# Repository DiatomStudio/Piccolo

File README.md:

# Piccolo, the tiny cnc bot #

A pocket sized open source CNC-bot.

Using laser-cutting, off-the-shelf hardware and Arduino, you can make your own simple 3 axis robot. Attach a brush or pen to make a quick drawing robot, or extend Piccolo with sensors, custom toolheads, or by using multiple Piccolos together. Experiment with 2D or 3D digital fabrication at a small scale!

For more info please see [www.piccolo.cc](http://www.piccolo.cc)

[Piccolo Flickr Pool](http://www.flickr.com/groups/1929303@N21/)

[www.diatom.cc](http://www.diatom.cc)

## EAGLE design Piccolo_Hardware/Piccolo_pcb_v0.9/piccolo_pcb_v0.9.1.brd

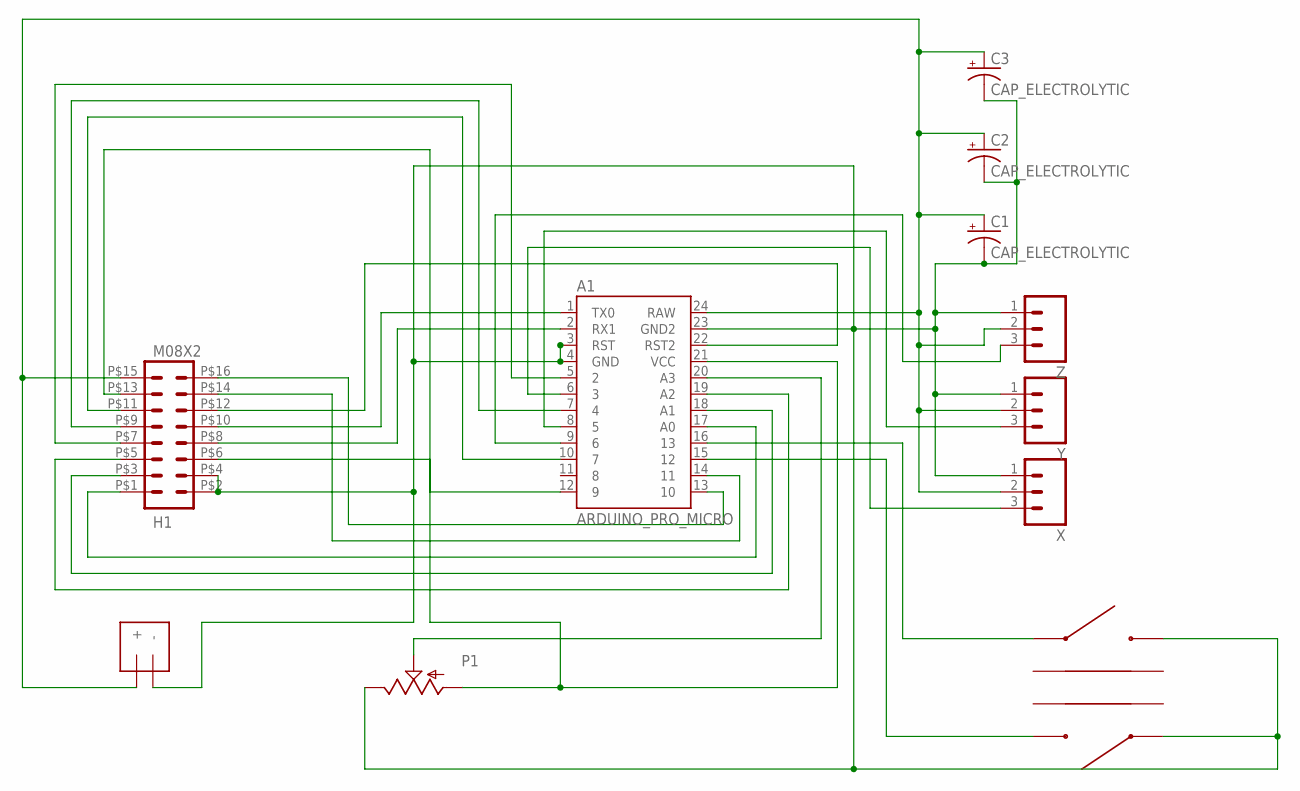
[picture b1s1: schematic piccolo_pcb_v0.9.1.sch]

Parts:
A1: ARDUINO_PRO_MICRO; ARDUINO_MINI
C1, C2, C3: CAP_ELECTROLYTIC; RADIAL_330UF
DC_IN: 4.8v-6.0v; JST-PH-2-PTH
H1: M08X2; PTH_2X8_90DEG_FEMALE
P1: POTTHUMBWHEEL; 16MM_THUMBWHEEL
S1, S2: SWITCH_TACTILE; RIGHT_ANGLE_TACTSWITCH
X: M03PTH; 1X03
Y: M03PTH; 1X03
Z: M03PTH; 1X03

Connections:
A3: A1.20 (A3), P1.P$2 (S)
GND: A1.3 (RST), A1.4 (GND), A1.23 (GND2), C1.C (-), C2.C (-), C3.C (-), DC_IN.-, H1.P$2 (2), H1.P$4 (4), P1.P$1 (E), S1.1, S2.2, X.1, Y.1, Z.1
unnamed: A1.15 (12), S1.2
unnamed: A1.16 (13), S2.1
PIN2: A1.5 (2), H1.P$7 (7)
PIN4: A1.7 (4), H1.P$9 (9)
PIN7: A1.10 (7), H1.P$11 (11)
PIN9: A1.12 (9), H1.P$13 (13)
PIN10: A1.13 (10), H1.P$16 (16)
PIN16: A1.14 (11), H1.P$14 (14)
PIN_A0: A1.17 (A0), H1.P$1 (1)
PIN_A1: A1.18 (A1), H1.P$3 (3)
PIN_A2: A1.19 (A2), H1.P$5 (5)
PWR_RAW: A1.24 (RAW), C1.A (+), C2.A (+), C3.A (+), DC_IN.+, H1.P$15 (15), X.2, Y.2, Z.2
RESET: A1.22 (RST2), H1.P$12 (12)
RX: A1.2 (RX1), H1.P$8 (8)
TX: A1.1 (TX0), H1.P$10 (10)
VCC: A1.21 (VCC), H1.P$6 (6), P1.P$3 (A)
X_PWM_PIN3: A1.6 (3), X.3
Y_PWM_PIN5: A1.8 (5), Y.3
Z_PWM_PIN6: A1.9 (6), Z.3

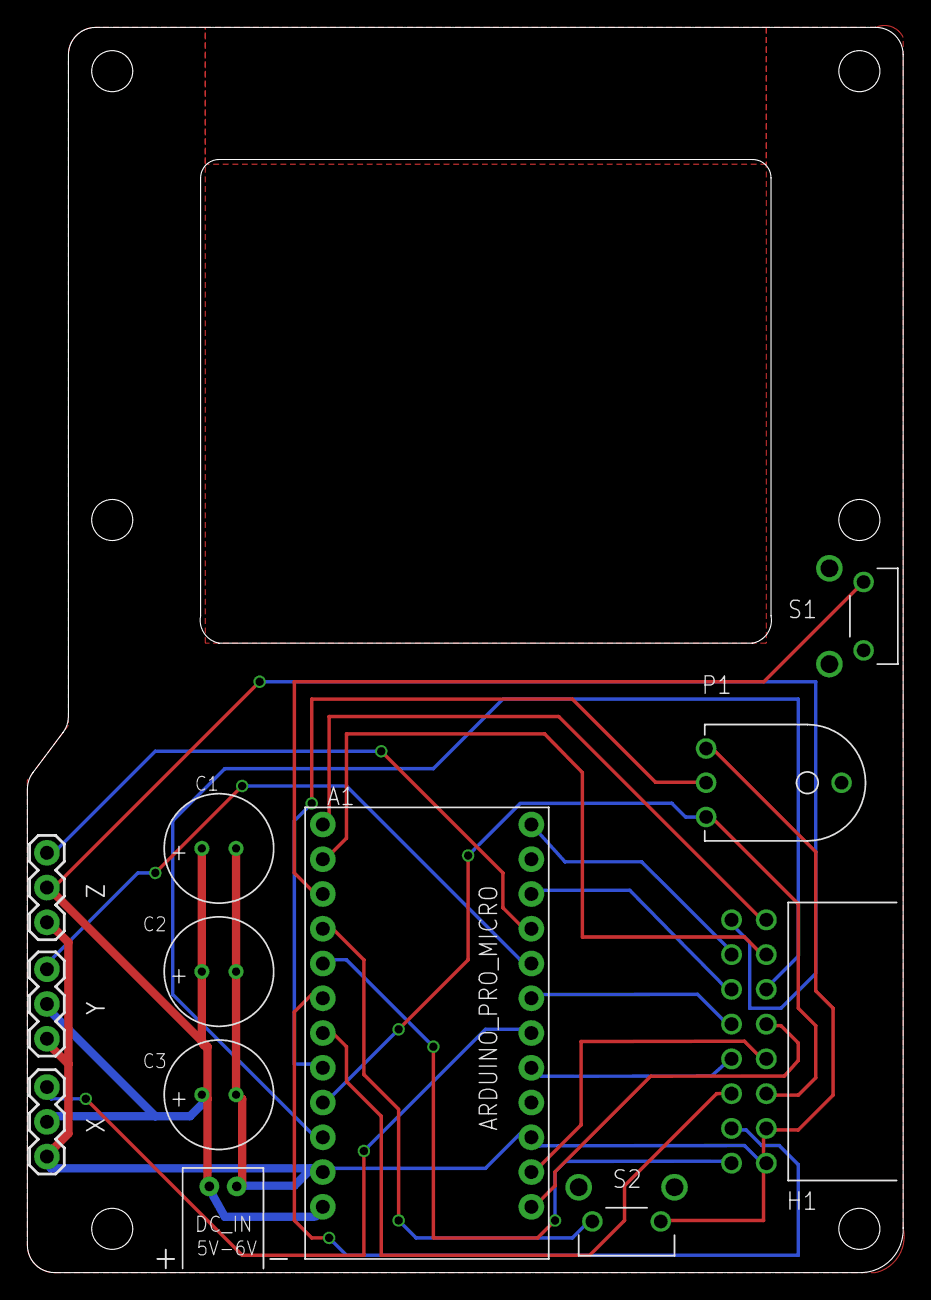
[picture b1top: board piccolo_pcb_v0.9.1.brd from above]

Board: 2 copper layers, 64.0 x 91.0 mm, 12 parts (0 on the bottom side), 21 nets.

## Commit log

2013-12-16 latest parts list
2013-12-16 subfolder readme?
2013-12-30 initial hardware commit
    + controllo & piccolo lib, sans readme
2014-01-03 PiccoloLib v0.2
    Firmware version loaded on TEI backers Piccolo’s
2014-01-07 added hardware archives
2014-01-07 add plotsi readme
2014-01-07 edit plotsi readme
2014-01-07 add telaio readme
2014-01-09 update STL rotations
2014-01-10 Controllo build 14
    -Added readme
    -Rescale drawings for new PiccoloLib v0.2
2014-01-10 Reorganise directory structure, PiccoloLib README
    Reorganise directory structure
    Added licence files
    PiccoloLib README
    Small spelling fixes in documentation.
2014-01-10 Changing to LGPL licence
2014-01-10 spell check.
2014-01-14 adjust t-slot on x-chassis to fit low profile nut
2014-01-16 minor update to piccolo v1 cutting pattern
2014-01-19 Scale set height value from Piccolo
    Scale set Z height values sent from Piccolo to controllo coordinates.
2014-01-19 testing git update
2014-01-20 Fixing slow move on first vertex
    Fixing slow move on first vertex, adding new examples.
2014-01-20 fixing wrong default
2014-01-21 fix bug in Piccolo.calcFloat(), add controllo Win/Mac binaries
2014-01-26 resize t-slots on x-chassis for low-profile nuts
2014-01-26 added pcb outline to cutting pattern
2014-01-26 added untabbed cutting pattern
2014-01-27 readme edit
2014-02-17 added license notice to cutting pattern
2014-02-17 updated CC BY-NC-SA license to 4.0
2014-02-17 updated archive with 4.0 license
2014-03-27 revised piccololib to be integrated with controllo
2014-03-27 added revised piccololib sources
2014-04-16 Fixing control to work with new PiccoloLib (in progress)
    Modifying control to work with new PiccoloLib
    -Changed PiccoloLib class name back to PiccoloLib from Piccolo
    -implemented sending coordinate as 32 bit signed ints.
2014-04-27 added Translate and popMatrix, reconfigured vertex commands.
    Reconfigured vertex command to add to processing internal vertex stack
    before being translated and scaled inside of controllo, this is because
    processing uses this internal stack to generate bezier vertex points.
2014-05-28 Changed Piccololib slightly serialLoop -> update(); added orientation functions to change drawing orientation. added PiccoloMeetProcessing library. PiccoloLib for processing, not supports transforms,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
2014-05-31 Added to Portrait prig, added button detect to Piccolo Processing Lib
2014-05-31 rotate
2014-07-10 Renamed PiccoloMeetProcessing to PiccoloP5.
    Renamed PiccoloMeetProcessing to PiccoloP5.
    Added Hello example to PiccoloP5.
    Adding additional documentation.
    Added PiccoloP5 library.
2014-07-10 updating to controllo 15
2014-07-10 restructuring
2014-07-10 format
2014-09-12 updated readme and piccolo v1.1 cutting patterns
2014-09-12 added piccolo_v1.1 cutting patterns
2014-09-14 reorganise
    Changed PiccoloP5 folder name from ProcessingP5 to PiccoloP5 (assume
    original name was from the processing library template)
    Added Control source to Controllo root folder instead of under source.
2014-10-04 Folder rearrange step 1
    New Projects folder
    Controllo has it’s own folder under Software
    Additional readme’s and code comments
2014-10-04 piccolo_v1.1 cutting files and updated readme
2014-10-05 Portrait
    Fixing up portrait to work with new version of PiccoloP5.
2014-10-05 readme
    TODO: add more infos
2014-10-05 added BezierYZ()
2014-10-05 bezierYZ() fix
2014-10-12 commented out unsused advanced piccoloAxis functions
2014-10-12 updated piccoloLib readme
2014-10-12 piccoloLib readme edit
2014-10-12 piccoloLib edit
2014-10-13 Piccolo IOT
    Added to PiccoloP5 the option of stream piccolo commands over Http
    instead of Serial, useful for sending piccolo commands from devices
    that do not have usb or serial ports.
    Added Android port of Control (work in progress)
    Small fixes in Controllo.
2014-10-16 Pre merge commit
    Checking for breaking changes before a push to release branch.
    PiccoloLib updated to v0.81 , new bezier function minor tidying up.
    PiccoloP5 updated to 0.91, code documentation added.
2014-10-16 Removed incompatible examples.
    Removed incompatible examples PiccoloLib
2014-10-16 Removed call to experimental feature.
2014-10-16 Updating PiccoloLib and Controllo versions to remove bugs,
2014-10-16 updated readme for launch!
2014-10-16 readded cutting v1 pattern
2014-10-19 fixed math in ellipse & arc
2014-10-19 updated v1 cutting patterns tabbed/untabbed
2014-10-20 piccoloP5 readme edit
2014-10-21 updated v1 partslist
2014-10-22 bringing branch up to date with master
2014-10-22 Commit before bringing develop branch in line with master.
2014-10-22 Updating Piccolo licenses to CC BY-SA.
2014-10-22 merging file missed in last merge
2014-10-22 updated license text in cutting patterns
2014-10-22 Updating file name.
2014-10-22 tidying up
2014-10-22 Removing unused file.
2015-02-06 Fixed syntax error
    extra 'x' found during a VHS workshop ;-)
2017-04-10 Update Controllo.pde
    Commentting two lines to make it work on Processing 3.3
2017-04-18 Fix broken Markdown headings

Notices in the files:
parts and their libraries:
SparkFun-Boards: Licensing: CC v3.0 Share-Alike You are welcome to use this library for commercial purposes.
